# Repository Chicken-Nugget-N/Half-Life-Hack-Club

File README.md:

# Half-Life-Hack-Club-starbie

Week 1: Starbie Starter Project
Made the starbie starter project because I don't have much experience with PCB CAD. Modified my starbie with Ultrasonic Sensor, LED, Potentiometer, and buzzer. Not sure how to implement them yet.

I decided to make this starbie because I needed an intro to pcb design during the Half life hack club. I'm really excited to do this project because I want to gain more experience with hardware and electronics. 
I started by following instructions on importing all the necessary footprints and schematics in KiCad, and then designed a schematic with sections for a screen, potentiometer, buttons and an LED.

Next thing, I wired up the pcb outline so that all the components were connected. I had some trouble until I realized there were two layers through which I could wire the pcb. That made it a lot simpler. Its still a messy wiring, but as my first cad, its not horrible

Next I worked on the program on Arduino IDE and modified the baseline code. I plan to iterate on this code during the build week once I have the physical copy and can see what everything is doing.

Finally, I assembled my BOM. Due to the lack of funding from starter projects and ridiculous PCB prices, I ended up only putting the PCB on the BOM and just bought everything else myself. The BOM in this repository is an accurate list of what I need funded, however below is an table of everything I have purchased

| Item | Amount | Cost (ea.) | Link |
|---|---:|---:|---|
| XIAO ESP32 C3 | 1 | $19.99 | [Amazon](https://www.amazon.com/XIAO-ESP32C3-3PCS-Pack-Bluetooth5-0/dp/B0DGX3LSC7/) |
| 0.96 OLED | 1 | $9.99 | [Amazon](https://www.amazon.com/dp/B0GBVWBWCR) |
| MPU6050 | 1 | $11.37 | [Amazon](https://www.amazon.com/hiBCTR-MPU-6050-Accelerometer-Gyroscope-Converter/dp/B0DTJY9B1D) |
| DHT11 | 1 | $9.99 | [Amazon](https://www.amazon.com/Teyleten-Robot-Temperature-Humidity-Raspberry/dp/B0CPF6ZZ73) |
| PCB | 1 | $26.32 | [JLCPCB](https://www.jlcpcb.com/) |
| **Total (each kit)** | **1** | **$77.66** | — |

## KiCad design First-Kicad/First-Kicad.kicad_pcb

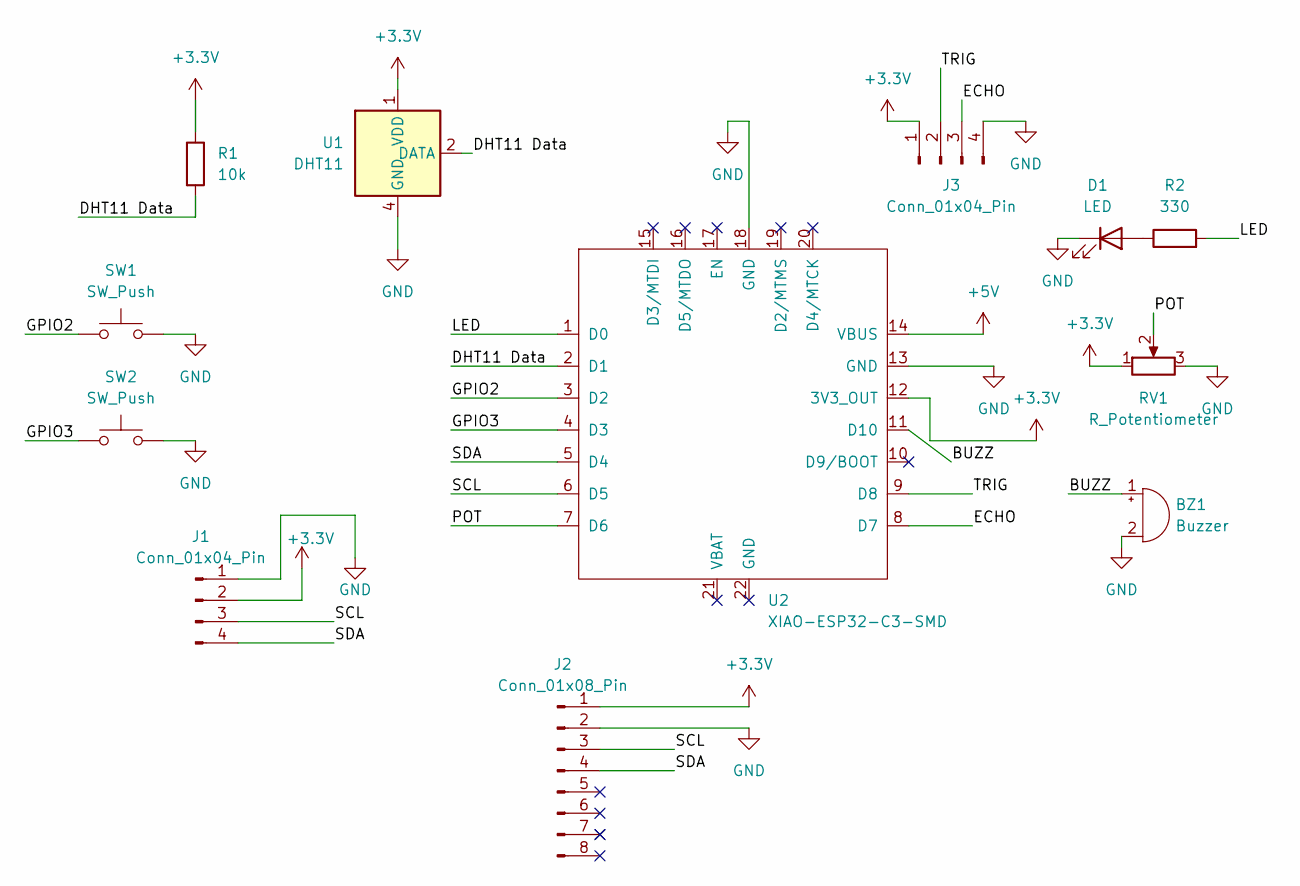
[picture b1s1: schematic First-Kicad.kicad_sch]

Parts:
BZ1: Buzzer; Buzzer_12x9.5RM7.6
D1: LED; LED_D5.0mm
J1: Conn_01x04_Pin; Display_128x64_096_I2C
J2: Conn_01x08_Pin; PinSocket_1x08_P2.54mm_Vertical
J3: Conn_01x04_Pin; PinSocket_1x04_P2.54mm_Vertical
R1: 10k; R_Axial_DIN0204_L3.6mm_D1.6mm_P7.62mm_Horizontal
R2: 330; R_Axial_DIN0204_L3.6mm_D1.6mm_P7.62mm_Horizontal
RV1: R_Potentiometer; Potentiometer_Alpha_RD901F-40-00D_Single_Vertical
SW1, SW2: SW_Push; SW_Cherry_MX_1.00u_PCB
U1: DHT11; Aosong_DHT11_5.5x12.0_P2.54mm
U2: XIAO-ESP32-C3-SMD

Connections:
+3.3V: J1.2, J2.1, J3.1, R1.1, RV1.1, U1.1 (VDD), U2.12 (3V3_OUT)
+5V: U2.14 (VBUS)
/BUZZ: BZ1.1 (+), U2.11 (D10)
/DHT11 Data: R1.2, U1.2 (DATA), U2.2 (D1)
/ECHO: J3.3, U2.8 (D7)
/GPIO2: SW1.1, U2.3 (D2)
/GPIO3: SW2.1, U2.4 (D3)
/LED: R2.2, U2.1 (D0)
/POT: RV1.2, U2.7 (D6)
/SCL: J1.3, J2.3, U2.6 (D5)
/SDA: J1.4, J2.4, U2.5 (D4)
/TRIG: J3.2, U2.9 (D8)
GND: BZ1.2 (-), D1.1 (K), J1.1, J2.2, J3.4, RV1.3, SW1.2, SW2.2, U1.4 (GND), U2.13 (GND), U2.18 (GND)
unnamed: D1.2 (A), R2.1

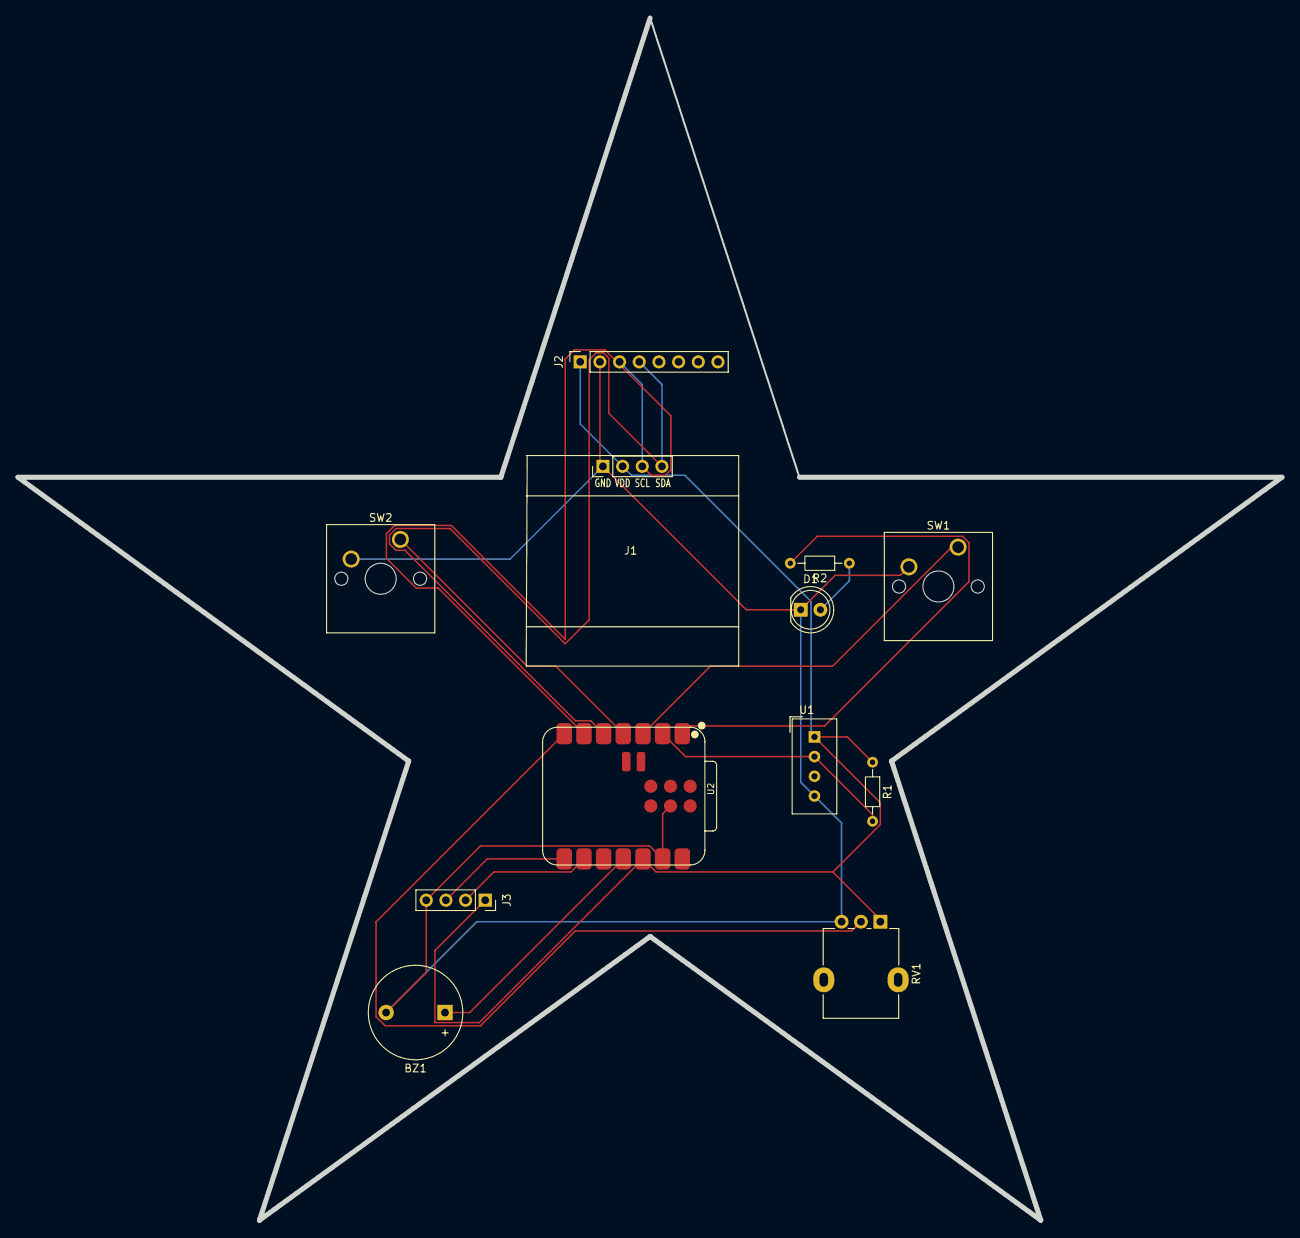
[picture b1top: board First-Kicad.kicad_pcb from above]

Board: 2 copper layers, 163.2 x 155.2 mm, 12 parts (0 on the bottom side), 13 nets.
